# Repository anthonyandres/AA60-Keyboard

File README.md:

# AA60-Keyboard

An introductory project to learning KiCad and PCB design. I've been in the custom keyboard hobby for a while now, and my first keyboard was a hand soldered keyboard. What better way to learn PCB design then with one of my favorite hobbies.

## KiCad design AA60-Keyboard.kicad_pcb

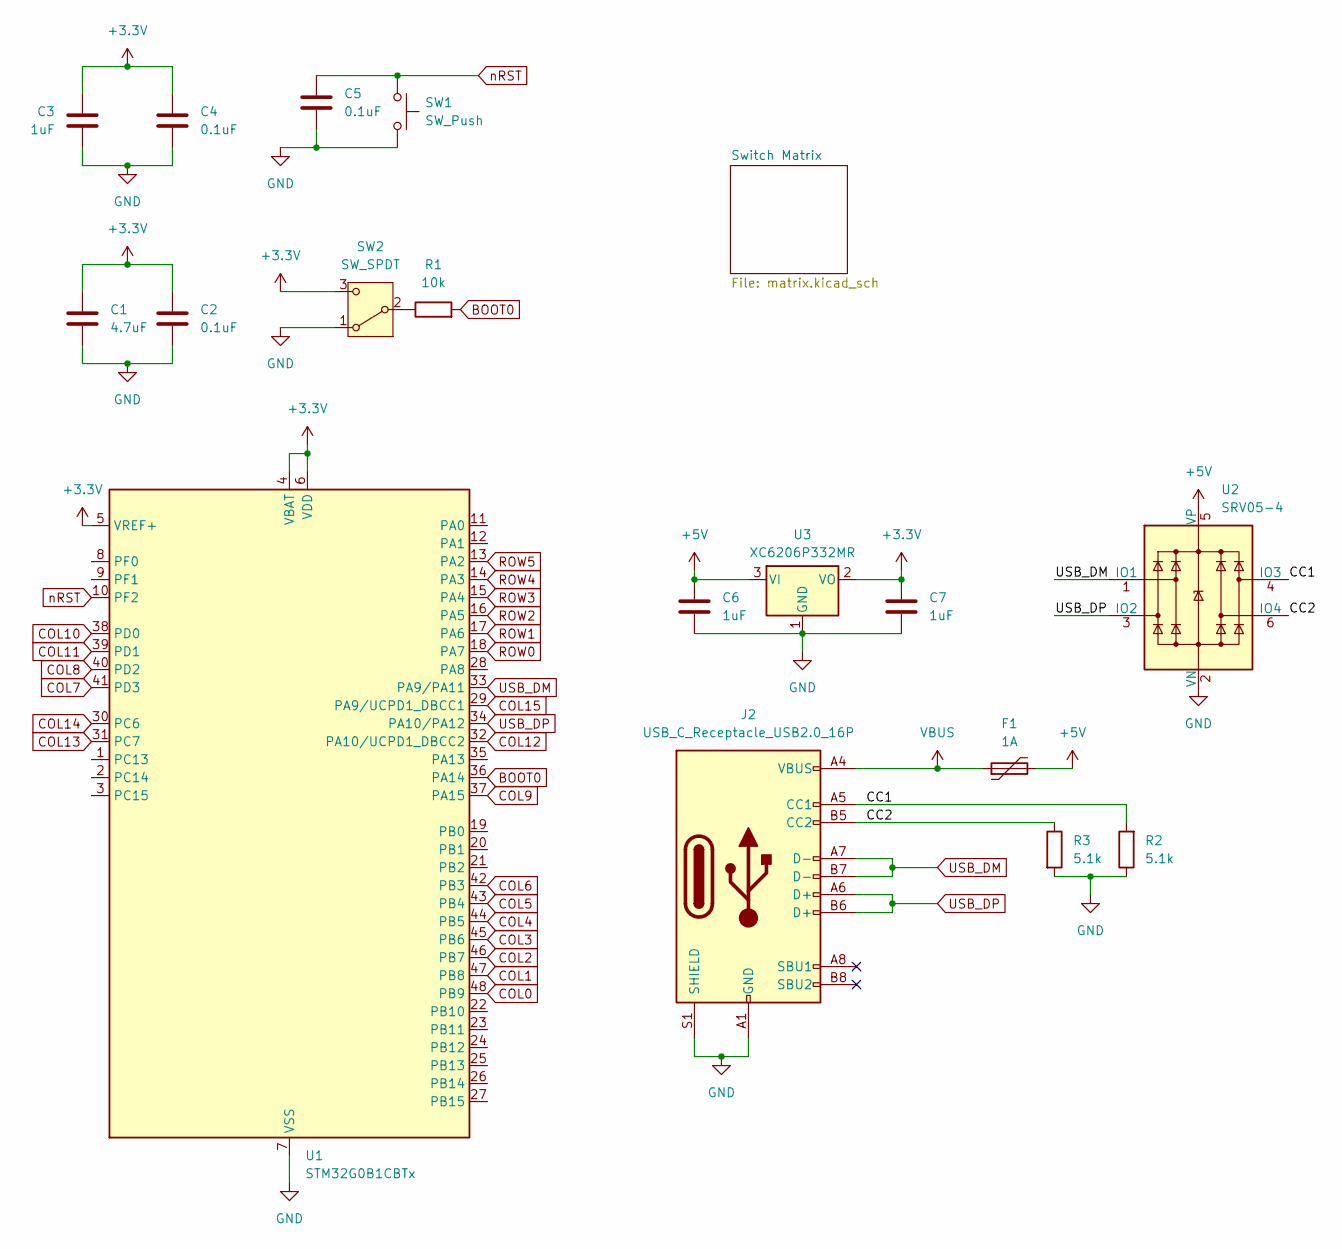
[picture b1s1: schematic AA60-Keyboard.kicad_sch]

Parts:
C1: 4.7uF; C_0805_2012Metric
C2, C4, C5: 0.1uF; C_0805_2012Metric
C3, C6, C7: 1uF; C_0805_2012Metric
F1: 1A; Fuse_1206_3216Metric
J2: USB_C_Receptacle_USB2.0_16P; USB_C_Receptacle_HRO_TYPE-C-31-M-12
R1: 10k; R_0805_2012Metric
R2, R3: 5.1k; R_0805_2012Metric
SW1: SW_Push; SW_SPST_TS-1088-xR020
SW2: SW_SPDT; SW_SPDT_PCM12
U1: STM32G0B1CBTx; LQFP-48_7x7mm_P0.5mm
U2: SRV05-4; SOT-23-6
U3: XC6206P332MR; SOT-23-3

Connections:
+3.3V: C1.1, C2.1, C3.1, C4.1, C7.1, SW2.3 (C), U1.4 (VBAT), U1.5 (VREF+), U1.6 (VDD), U3.2 (VO)
+5V: C6.1, F1.2, U2.5 (VP), U3.3 (VI)
/CC1: J2.A5 (CC1), R2.2, U2.4 (IO3)
/CC2: J2.B5 (CC2), R3.1, U2.6 (IO4)
BOOT0: R1.2, U1.36 (PA14)
COL0: U1.48 (PB9); also elsewhere on the board
COL1: U1.47 (PB8); also elsewhere on the board
COL2: U1.46 (PB7); also elsewhere on the board
COL3: U1.45 (PB6); also elsewhere on the board
COL4: U1.44 (PB5); also elsewhere on the board
COL5: U1.43 (PB4); also elsewhere on the board
COL6: U1.42 (PB3); also elsewhere on the board
COL7: U1.41 (PD3); also elsewhere on the board
COL8: U1.40 (PD2); also elsewhere on the board
COL9: U1.37 (PA15); also elsewhere on the board
COL10: U1.38 (PD0); also elsewhere on the board
COL11: U1.39 (PD1); also elsewhere on the board
COL12: U1.32 (PA10/UCPD1_DBCC2); also elsewhere on the board
COL13: U1.31 (PC7); also elsewhere on the board
COL14: U1.30 (PC6); also elsewhere on the board
COL15: U1.29 (PA9/UCPD1_DBCC1); also elsewhere on the board
GND: C1.2, C2.2, C3.2, C4.2, C5.2, C6.2, C7.2, J2.A1 (GND), J2.A12 (GND), J2.B1 (GND), J2.B12 (GND), J2.S1 (SHIELD), R2.1, R3.2, SW1.2, SW2.1 (A), U1.7 (VSS), U2.2 (VN), U3.1 (GND)
unnamed: R1.1, SW2.2 (B)
ROW0: U1.18 (PA7); also elsewhere on the board
ROW1: U1.17 (PA6); also elsewhere on the board
ROW2: U1.16 (PA5); also elsewhere on the board
ROW3: U1.15 (PA4); also elsewhere on the board
ROW4: U1.14 (PA3); also elsewhere on the board
ROW5: U1.13 (PA2); also elsewhere on the board
USB_DM: J2.A7 (D-), J2.B7 (D-), U1.33 (PA9/PA11), U2.1 (IO1)
USB_DP: J2.A6 (D+), J2.B6 (D+), U1.34 (PA10/PA12), U2.3 (IO2)
VBUS: F1.1, J2.A4 (VBUS), J2.A9 (VBUS), J2.B4 (VBUS), J2.B9 (VBUS)
nRST: C5.1, SW1.1, U1.10 (PF2)

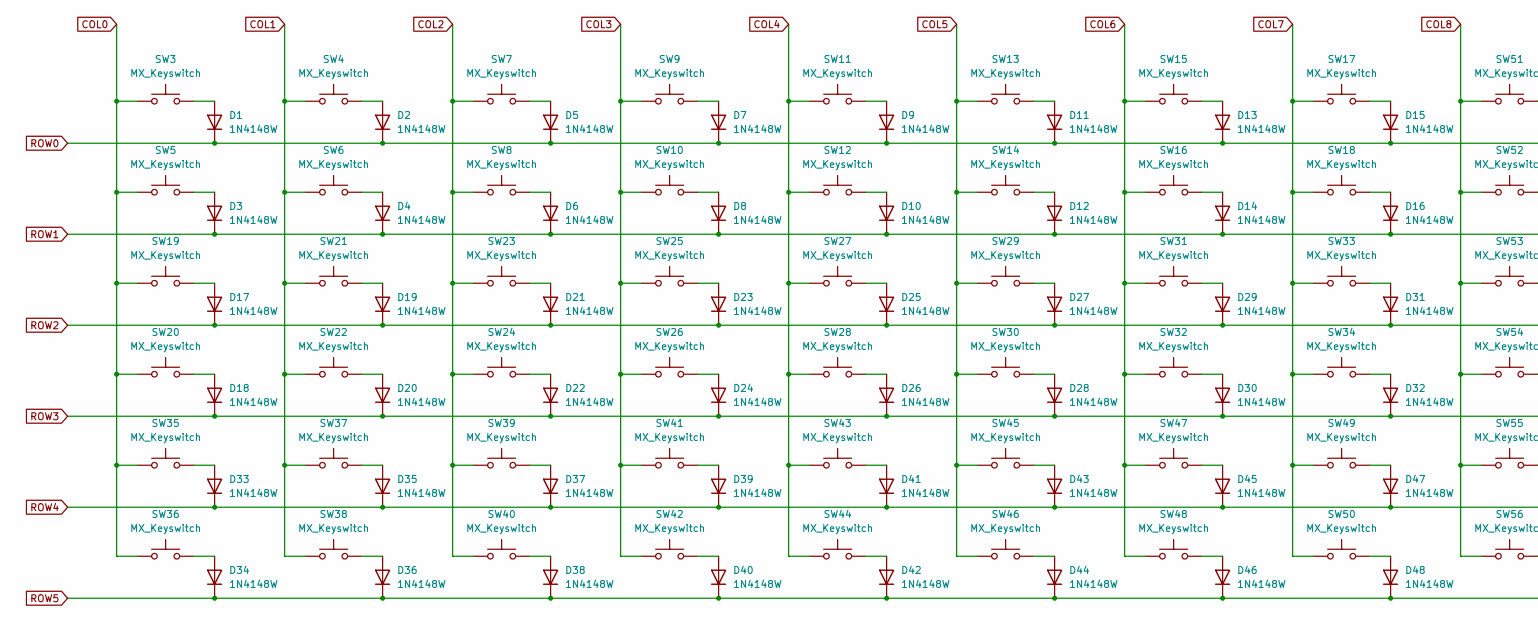
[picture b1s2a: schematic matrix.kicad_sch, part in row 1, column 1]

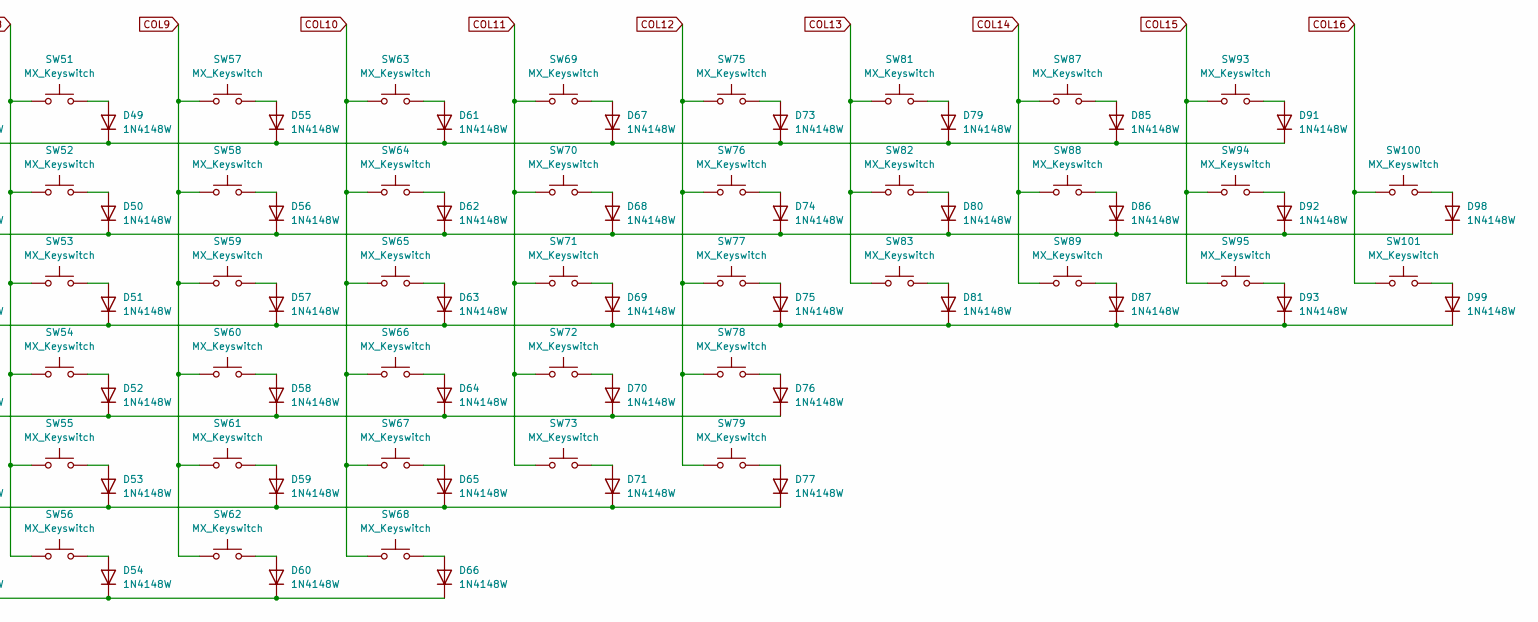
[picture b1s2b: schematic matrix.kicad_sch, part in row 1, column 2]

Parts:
D1, D2, D3, D4, D5, D6, D7, D8, D9, D10, D11, D12, D13, D14, D15, D16, D17, D18, D19, D20, D21, D22, D23, D24, D25, D26, D27, D28, D29, D30, D31, D32, D33, D34, D35, D36, D37, D38, D39, D40, D41, D42, D43, D44, D45, D46, D47, D48, D49, D50, D51, D52, D53, D54, D55, D56, D57, D58, D59, D60, D61, D62, D63, D64, D65, D66, D67, D68, D69, D70, D71, D73, D74, D75, D76, D77, D79, D80, D81, D85, D86, D87, D91, D92, D93, D98, D99: 1N4148W; D_SOD-123
SW3, SW4, SW5, SW6, SW7, SW8, SW9, SW10, SW11, SW12, SW13, SW14, SW15, SW16, SW17, SW18, SW21, SW22, SW23, SW24, SW25, SW26, SW27, SW28, SW29, SW30, SW31, SW32, SW33, SW34, SW37, SW39, SW41, SW43, SW45, SW47, SW49, SW51, SW52, SW53, SW54, SW55, SW56, SW57, SW58, SW59, SW60, SW61, SW62, SW63, SW64, SW65, SW66, SW67, SW68, SW69, SW70, SW71, SW72, SW75, SW76, SW77, SW79, SW81, SW87, SW88, SW89, SW93, SW94, SW95, SW100, SW101: MX_Keyswitch; MX-Solderable-1U
SW19, SW83: MX_Keyswitch; MX-Solderable-1.5U
SW20: MX_Keyswitch; MX-Solderable-1.75U
SW35, SW78: MX_Keyswitch; MX-Solderable-2.25U
SW36, SW38, SW40, SW44, SW46, SW48, SW50: MX_Keyswitch; MX-Solderable-1.25U
SW42: MX_Keyswitch; MX-Solderable-6.25U
SW73: MX_Keyswitch; MX-Solderable-2.75U
SW82: MX_Keyswitch; MX-Solderable-2U

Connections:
COL0: SW3.1, SW5.1, SW19.1, SW20.1, SW35.1, SW36.1; also elsewhere on the board
COL1: SW4.1, SW6.1, SW21.1, SW22.1, SW37.1, SW38.1; also elsewhere on the board
COL2: SW7.1, SW8.1, SW23.1, SW24.1, SW39.1, SW40.1; also elsewhere on the board
COL3: SW9.1, SW10.1, SW25.1, SW26.1, SW41.1, SW42.1; also elsewhere on the board
COL4: SW11.1, SW12.1, SW27.1, SW28.1, SW43.1, SW44.1; also elsewhere on the board
COL5: SW13.1, SW14.1, SW29.1, SW30.1, SW45.1, SW46.1; also elsewhere on the board
COL6: SW15.1, SW16.1, SW31.1, SW32.1, SW47.1, SW48.1; also elsewhere on the board
COL7: SW17.1, SW18.1, SW33.1, SW34.1, SW49.1, SW50.1; also elsewhere on the board
COL8: SW51.1, SW52.1, SW53.1, SW54.1, SW55.1, SW56.1; also elsewhere on the board
COL9: SW57.1, SW58.1, SW59.1, SW60.1, SW61.1, SW62.1; also elsewhere on the board
COL10: SW63.1, SW64.1, SW65.1, SW66.1, SW67.1, SW68.1; also elsewhere on the board
COL11: SW69.1, SW70.1, SW71.1, SW72.1, SW73.1; also elsewhere on the board
COL12: SW75.1, SW76.1, SW77.1, SW78.1, SW79.1; also elsewhere on the board
COL13: SW81.1, SW82.1, SW83.1; also elsewhere on the board
COL14: SW87.1, SW88.1, SW89.1; also elsewhere on the board
COL15: SW93.1, SW94.1, SW95.1; also elsewhere on the board
COL16: SW100.1, SW101.1
unnamed: D1.2 (A), SW3.2
unnamed: D2.2 (A), SW4.2
unnamed: D3.2 (A), SW5.2
unnamed: D4.2 (A), SW6.2
unnamed: D5.2 (A), SW7.2
unnamed: D6.2 (A), SW8.2
unnamed: D7.2 (A), SW9.2
unnamed: D8.2 (A), SW10.2
unnamed: D9.2 (A), SW11.2
unnamed: D10.2 (A), SW12.2
unnamed: D11.2 (A), SW13.2
unnamed: D12.2 (A), SW14.2
unnamed: D13.2 (A), SW15.2
unnamed: D14.2 (A), SW16.2
unnamed: D15.2 (A), SW17.2
unnamed: D16.2 (A), SW18.2
unnamed: D17.2 (A), SW19.2
unnamed: D18.2 (A), SW20.2
unnamed: D19.2 (A), SW21.2
unnamed: D20.2 (A), SW22.2
unnamed: D21.2 (A), SW23.2
unnamed: D22.2 (A), SW24.2
unnamed: D23.2 (A), SW25.2
unnamed: D24.2 (A), SW26.2
unnamed: D25.2 (A), SW27.2
unnamed: D26.2 (A), SW28.2
unnamed: D27.2 (A), SW29.2
unnamed: D28.2 (A), SW30.2
unnamed: D29.2 (A), SW31.2
unnamed: D30.2 (A), SW32.2
unnamed: D31.2 (A), SW33.2
unnamed: D32.2 (A), SW34.2
unnamed: D33.2 (A), SW35.2
unnamed: D34.2 (A), SW36.2
unnamed: D35.2 (A), SW37.2
unnamed: D36.2 (A), SW38.2
unnamed: D37.2 (A), SW39.2
unnamed: D38.2 (A), SW40.2
unnamed: D39.2 (A), SW41.2
unnamed: D40.2 (A), SW42.2
unnamed: D41.2 (A), SW43.2
unnamed: D42.2 (A), SW44.2
unnamed: D43.2 (A), SW45.2
unnamed: D44.2 (A), SW46.2
unnamed: D45.2 (A), SW47.2
unnamed: D46.2 (A), SW48.2
unnamed: D47.2 (A), SW49.2
unnamed: D48.2 (A), SW50.2
unnamed: D49.2 (A), SW51.2
unnamed: D50.2 (A), SW52.2
unnamed: D51.2 (A), SW53.2
unnamed: D52.2 (A), SW54.2
unnamed: D53.2 (A), SW55.2
unnamed: D54.2 (A), SW56.2
unnamed: D55.2 (A), SW57.2
unnamed: D56.2 (A), SW58.2
unnamed: D57.2 (A), SW59.2
unnamed: D58.2 (A), SW60.2
unnamed: D59.2 (A), SW61.2
unnamed: D60.2 (A), SW62.2
unnamed: D61.2 (A), SW63.2
unnamed: D62.2 (A), SW64.2
unnamed: D63.2 (A), SW65.2
unnamed: D64.2 (A), SW66.2
unnamed: D65.2 (A), SW67.2
unnamed: D66.2 (A), SW68.2
unnamed: D67.2 (A), SW69.2
unnamed: D68.2 (A), SW70.2
unnamed: D69.2 (A), SW71.2
unnamed: D70.2 (A), SW72.2
unnamed: D71.2 (A), SW73.2
unnamed: D73.2 (A), SW75.2
unnamed: D74.2 (A), SW76.2
unnamed: D75.2 (A), SW77.2
unnamed: D76.2 (A), SW78.2
unnamed: D77.2 (A), SW79.2
unnamed: D79.2 (A), SW81.2
unnamed: D80.2 (A), SW82.2
unnamed: D81.2 (A), SW83.2
unnamed: D85.2 (A), SW87.2
unnamed: D86.2 (A), SW88.2
unnamed: D87.2 (A), SW89.2
unnamed: D91.2 (A), SW93.2
unnamed: D92.2 (A), SW94.2
unnamed: D93.2 (A), SW95.2
unnamed: D98.2 (A), SW100.2
unnamed: D99.2 (A), SW101.2
ROW0: D1.1 (K), D2.1 (K), D5.1 (K), D7.1 (K), D9.1 (K), D11.1 (K), D13.1 (K), D15.1 (K), D49.1 (K), D55.1 (K), D61.1 (K), D67.1 (K), D73.1 (K), D79.1 (K), D85.1 (K), D91.1 (K); also elsewhere on the board
ROW1: D3.1 (K), D4.1 (K), D6.1 (K), D8.1 (K), D10.1 (K), D12.1 (K), D14.1 (K), D16.1 (K), D50.1 (K), D56.1 (K), D62.1 (K), D68.1 (K), D74.1 (K), D80.1 (K), D86.1 (K), D92.1 (K), D98.1 (K); also elsewhere on the board
ROW2: D17.1 (K), D19.1 (K), D21.1 (K), D23.1 (K), D25.1 (K), D27.1 (K), D29.1 (K), D31.1 (K), D51.1 (K), D57.1 (K), D63.1 (K), D69.1 (K), D75.1 (K), D81.1 (K), D87.1 (K), D93.1 (K), D99.1 (K); also elsewhere on the board
ROW3: D18.1 (K), D20.1 (K), D22.1 (K), D24.1 (K), D26.1 (K), D28.1 (K), D30.1 (K), D32.1 (K), D52.1 (K), D58.1 (K), D64.1 (K), D70.1 (K), D76.1 (K); also elsewhere on the board
ROW4: D33.1 (K), D35.1 (K), D37.1 (K), D39.1 (K), D41.1 (K), D43.1 (K), D45.1 (K), D47.1 (K), D53.1 (K), D59.1 (K), D65.1 (K), D71.1 (K), D77.1 (K); also elsewhere on the board
ROW5: D34.1 (K), D36.1 (K), D38.1 (K), D40.1 (K), D42.1 (K), D44.1 (K), D46.1 (K), D48.1 (K), D54.1 (K), D60.1 (K), D66.1 (K); also elsewhere on the board

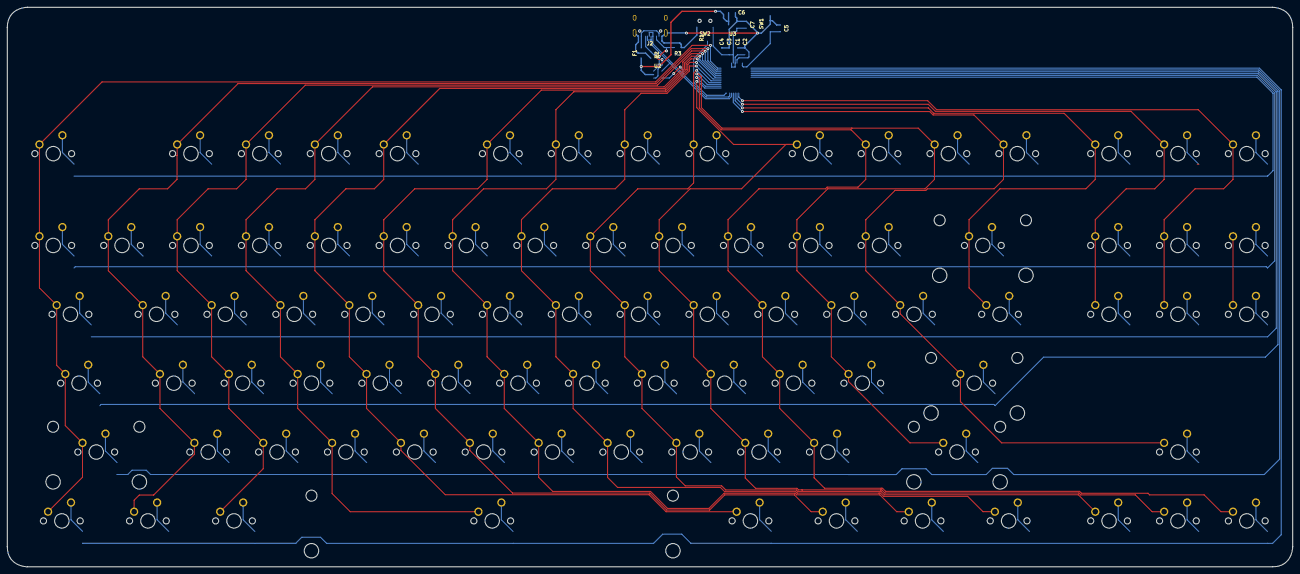
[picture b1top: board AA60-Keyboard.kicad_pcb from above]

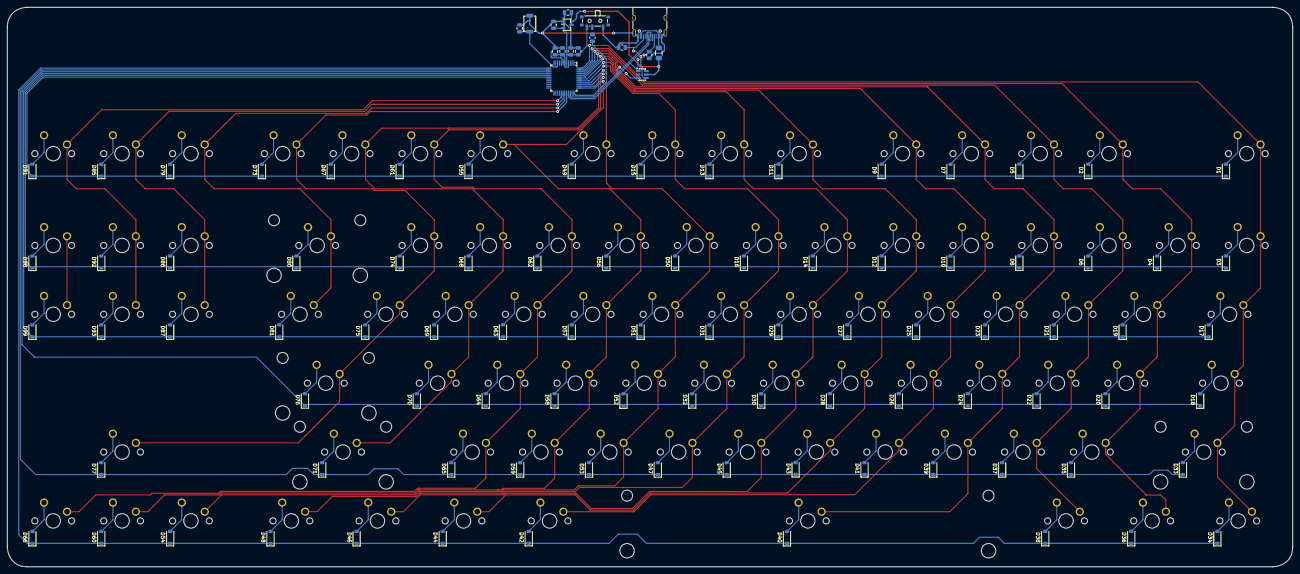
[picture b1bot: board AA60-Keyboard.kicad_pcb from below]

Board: 2 copper layers, 355.6 x 154.8 mm, 191 parts (104 on the bottom side), 121 nets.

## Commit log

2026-03-17 KiCad init
2026-03-17 Added Submodules
2026-03-17 MCU/USB/Switch Matrix Schematics
2026-03-18 Footprints
2026-03-18 PCB Changes
2026-03-18 Putting diodes in their place
2026-03-20 PCB matrix front and back traces
2026-03-22 Microcontroller Circuitry
2026-03-23 USB and microcontroller circuits wired (is ESD for CC lines needed??)
2026-03-26 Microcontroller Matrix Routed
